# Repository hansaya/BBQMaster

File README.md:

# BBQMaster
8 channel temperature monitor for barbecuing.

# Features
* 4 NTC thermistor channels.
* 4 K-type thermocouple channels.
* Web interface to monitor the temperatures.
* MQTT support with hassio auto discovery.
* OTA updates.
* Web portal.

# Background
I got into smoking meat last few years and figured out maintaining the temperature is a big part of getting juicy results. Like everyone else, I do not have patience to stay right next to the smoker to monitor the temps. Specially if you have a cheaper lower-end smoker; monitoring the temperature is crucial. The usual solution is to buy a wireless temp monitor out of Amazon so if you find one that works for you, go for it. My solution here is expensive, close to 100$. I ended up creating this project because I broke two sub 50$ sensors and a upgrade will cost around 100$. Hence I decided to make one knowing I can create one less than 100$ plus I had fun creating it.

I had few requirements.
1) Monitor temperature over a web interface or a app.
2) Wireless.
3) Enough probes to monitor every corner of a brisket.
4) Be able to monitor the inside of the smoker and maybe the fire box.

Knowing the requirements, I decided to go with
1) 4 NTC probe inputs since its easy to find commercial probes online.
2) 4 thermocouple inputs for higher temperature monitoring. Why? NTC probes cannot handle high heat. They will degrade really fast when you put them over 300F.
3) Use esp32 as the brain because its cheap and easy to program.

# How to order and build the board
Board files are in "boards/" folder. Design in Eagle and you can just drop the zip file located in baord/bbqsensor/cam/ into jlcpcb.com to get them made.

Board design:
* 100mmx54mm 2-layer board.
* Jelly bean parts are 603 or above.
* Uses CP2104 as the USB interface.
* Buck coveter based on TPS54331DR. This will allow 9v-24v input.
* Lipo charging based on MCP73831.
* 3v3 Regulator based on AP2112.
* Thermocouple input handled by OneWire MAX3185.
* NTC thermistors are monitored by ADS1115 ADC for better accuracy.
* ESP32 as the brain.
* Terminal block connectors for easy connections.

For the bom, look at the schematic.

DISCLAIMER:
I'm a amature designer. I would recommend going over the schematic before ordering.

## Probes

### NTC
Most common replacement bbq probes will work. I bought https://www.ebay.com/itm/Chugod-Grilling-BBQ-Meat-Thermometer-Probe-Replacement-Temperature-Probes-4-Pa/402310429902?hash=item5dab91fcce:g:aDoAAOSwulde-Xr3

### K-type
You can buy any shape or size you want. However it is very hard to find probes designed for food. I would recommend use the thermocouple probes just to measure the inside temperature or firebox temperature.

# How to compile.
1) Download and install vscode with platformio. https://platformio.org/
2) Modify the platformio.ini file to either use serial port or use over the air updates.
3) If you are using Windows to compile, you might run into an compiler error because of Timelib. There are two headers named time.h in esp32 core and Time.h in Arduino timelib. These two looks the same to the compiler in windows because windows file names are case insensitive. Solution is to delete .pio/libdeps/myenv/Time/Time.h. More info https://github.com/esp8266/Arduino/issues/2341
4) Press upload.
5) Upload SPIFF image by running the vscode task "Upload File System Image". You can get to the task list from the left platformio panel or by typing "CTRL+SHIFT+P->Run task->platformio->Upload file system image".

# How to configure.
Firmware needs to know the MQTT server configuration. This can be done using WIFI manager portal. 
When you upload the code, if there is no previous credentials saved in the memory, WIFI AP will starts to broadcast using the name BBQ_Master. Connect to it and use the web portal to enter in the WIFI info as well as MQTT server address and the port. This creates a file in SPIFF called config.json. If you failed to enter the correct information or wants to modify the configuration later, create a file name config.json with data/ folder then use the "Upload file system Image" task to push the new file out.
config.json should looks like:
``
{"mqtt_server":"example.com", "mqtt_port":"1883"}
``

## Home Assistant
Turn on MQTT auto discovery https://www.home-assistant.io/docs/mqtt/discovery/. If esp32 connected to the MQTT server then hassio will automatically discover the device. If you are using non default discovery_prefix within hassio then change MQTT_HOME_ASSISTANT_DISCOVERY_PREFIX within the code reflect it.

# Known issues
* Forgot to add a LED indicator to the board.
* There is no way to turn off. As a workaround I attached a switch in series with the battery.
* Pubsub library only let you add a one "will" message. Because of this hassio sometimes fails to put all temperature sensor into unavailable state when disconnecting power from the device.
* Web interface theme functionality is broken.

# Todo
* Clean up the web interface.
* Add the ability to configure the temperature probe names through the web interface.
* Ability to calibrate the temperature probes using the web interface.
* Add a proper gauge to the battery indicator in the web interface.

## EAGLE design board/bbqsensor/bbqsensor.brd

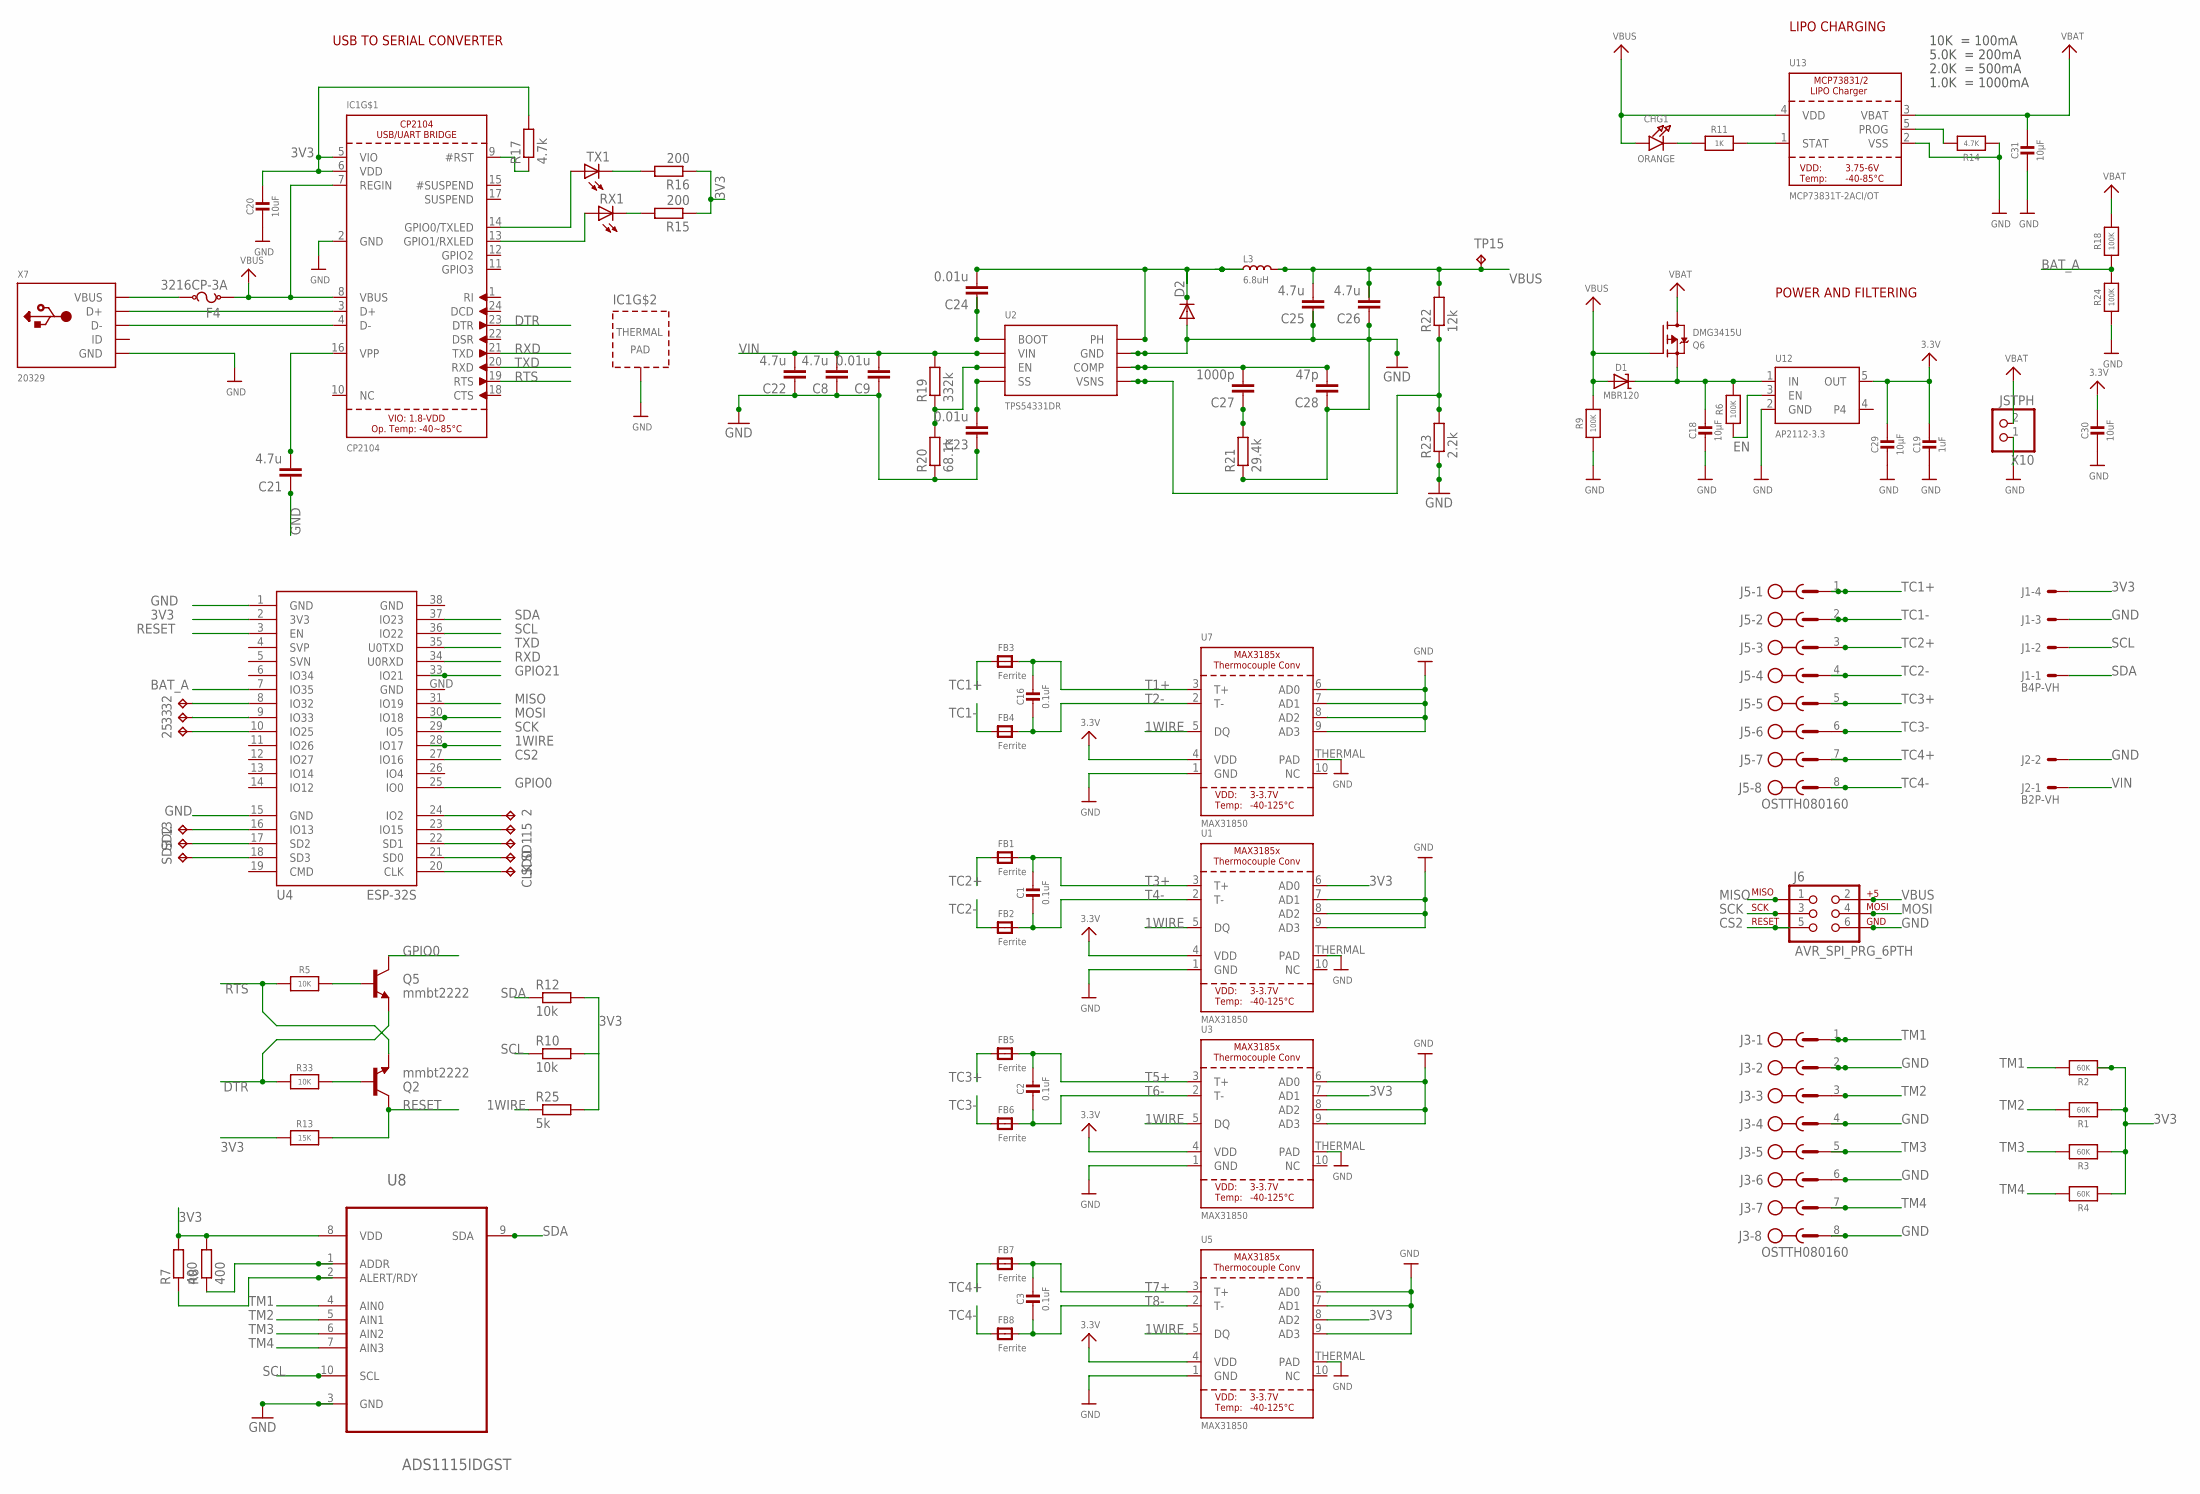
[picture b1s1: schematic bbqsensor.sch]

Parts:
2, 13, 15, 25, 32, 33: TPB1,27; B1,27
C1, C2, C3, C16: 0.1uF; 0805-NO
C8, C22, C25, C26: 4.7u; C1206
C9, C23, C24: 0.01u; C1206
C18, C29, C31: 10µF; 0805-NO
C19: 1uF; 0603-NO
C20, C30: 10uF; 0805-NO
C21: 4.7u; C1005
C27: 1000p; C1206
C28: 47p; C1206
CHG1: ORANGE; CHIPLED_0805_NOOUTLINE
CLK: TPB1,27; B1,27
D1: MBR120; SOD-123
D2: DIODE-DO214AA; DO214AA
F4: 3216CP-3A
FB1, FB2, FB3, FB4, FB5, FB6, FB7, FB8: Ferrite; 0805
IC1: CP2104; QFN24_4MM_SMSC
J1: B4P-VH; B4P
J2: B2P-VH; B2P
J3, J5: OSTTH080160; EDSTL130-08
J6: AVR_SPI_PRG_6PTH; 2X3
L3: 6.8uH; L1813
Q2, Q5: mmbt2222; SOT23-3
Q6: DMG3415U; SOT23-R
R1, R2, R3, R4: 60K; 0603-NO
R5, R33: 10K; 0603-NO
R6, R9, R18, R24: 100K; 0603-NO
R7, R8: 400; R0603
R10, R12: 10k; R0603
R11: 1K; 0603-NO
R13: 15K; 0603-NO
R14: 4.7K; 0603-NO
R15, R16: 200; R0603
R17: 4.7k; R0603
R19: 332k; R0603
R20: 68.1k; R0603
R21: 29.4k; R0603
R22: 12k; R0603
R23: 2.2k; R0603
R25: 5k; R0603
RX1: LEDSML0805; SML0805
SD0, SD1, SD2, SD3: TPB1,27; B1,27
TP15: TPB1,27; B1,27
TX1: LEDSML0805; SML0805
U1, U3, U5, U7: MAX31850; TDFN10_3X4MM
U2: TPS54331DR; SOIC-8
U4: ESP-32S
U8: ADS1115IDGST; SOP50P490X110-10N
U12: AP2112-3.3; SOT23-5
U13: MCP73831T-2ACI/OT; SOT23-5
X7: 20329; 4UCONN_20329_V2
X10: JSTPH; JSTPH2

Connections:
1WIRE: R25.1, U1.5 (DQ), U3.5 (DQ), U4.28 (IO17), U5.5 (DQ), U7.5 (DQ)
3V3: C19.1, C20.1, C29.1, C30.1, IC1.5 (VIO), IC1.6 (VDD), J1.4, R1.1, R2.1, R3.1, R4.1, R7.2, R8.2, R10.2, R12.2, R13.1, R15.1, R16.1, R17.2, R25.2, U1.4 (VDD), U1.6 (AD0), U3.4 (VDD), U3.7 (AD1), U4.2 (3V3), U5.4 (VDD), U5.8 (AD2), U7.4 (VDD), U8.8 (VDD), U12.5 (OUT)
BAT_A: R18.1, R24.2, U4.7 (IO35)
CS2: J6.5, U4.27 (IO16)
DTR: IC1.23 (DTR), Q5.2 (E), R33.1
EN: R6.1, U12.3 (EN)
GND: C8.1, C9.1, C18.2, C19.2, C20.2, C21.1, C22.1, C23.1, C25.1, C26.1, C28.1, C29.2, C30.2, C31.2, D2.A, IC1.2 (GND), IC1.THERM (TP), J1.3, J2.2, J3.2, J3.4, J3.6, J3.8, J6.6, R9.1, R14.1, R20.1, R21.1, R23.1, R24.1, U1.1 (GND), U1.7 (AD1), U1.8 (AD2), U1.9 (AD3), U1.THERMAL (PAD), U2.7 (GND), U3.1 (GND), U3.6 (AD0), U3.8 (AD2), U3.9 (AD3), U3.THERMAL (PAD), U4.1 (GND), U4.15 (GND), U4.38 (GND), U4.GND, U5.1 (GND), U5.6 (AD0), U5.7 (AD1), U5.9 (AD3), U5.THERMAL (PAD), U7.1 (GND), U7.6 (AD0), U7.7 (AD1), U7.8 (AD2), U7.9 (AD3), U7.THERMAL (PAD), U8.3 (GND), U12.2 (GND), U13.2 (VSS), X7.BASE@1 (GND), X7.BASE@2 (GND), X7.GND, X7.SPRT@1 (GND), X7.SPRT@2 (GND), X7.SPRT@3 (GND), X7.SPRT@4 (GND), X10.1
GPIO0: Q5.3 (C), U4.25 (IO0)
GPIO21: U4.33 (IO21)
MISO: J6.1, U4.31 (IO19)
MOSI: J6.4, U4.30 (IO18)
unnamed: 32.TP, U4.8 (IO32)
unnamed: 33.TP, U4.9 (IO33)
unnamed: 25.TP, U4.10 (IO25)
unnamed: 2.TP, U4.24 (IO2)
unnamed: 15.TP, U4.23 (IO15)
unnamed: 13.TP, U4.16 (IO13)
unnamed: SD1.TP, U4.22 (SD1)
unnamed: SD0.TP, U4.21 (SD0)
unnamed: CLK.TP, U4.20 (CLK)
unnamed: SD3.TP, U4.18 (SD3)
unnamed: SD2.TP, U4.17 (SD2)
unnamed: R7.1, U8.2 (ALERT/RDY)
unnamed: R8.1, U8.1 (ADDR)
unnamed: IC1.3 (D+), X7.D+
unnamed: IC1.4 (D-), X7.D-
unnamed: IC1.13 (GPIO1/RXLED), RX1.A
unnamed: R15.2, RX1.C
unnamed: R16.2, TX1.C
unnamed: IC1.14 (GPIO0/TXLED), TX1.A
unnamed: C18.1, D1.C, Q6.2 (S), R6.2, U12.1 (IN)
unnamed: CHG1.C, R11.1
unnamed: R11.2, U13.1 (STAT)
unnamed: R14.2, U13.5 (PROG)
unnamed: C21.2, IC1.16 (VPP)
unnamed: IC1.9 (#RST), R17.1
unnamed: F4.2, X7.VBUS
unnamed: Q2.1 (B), R33.2
unnamed: Q5.1 (B), R5.2
unnamed: C23.2, U2.4 (SS)
unnamed: R19.1, R20.2, U2.3 (EN)
unnamed: C24.1, U2.1 (BOOT)
unnamed: C24.2, D2.C, L3.1, U2.8 (PH)
unnamed: C27.2, C28.2, U2.6 (COMP)
unnamed: C27.1, R21.2
unnamed: R22.1, R23.2, U2.5 (VSNS)
RESET: Q2.3 (C), R13.2, U4.3 (EN)
RTS: IC1.19 (RTS), Q2.2 (E), R5.1
RXD: IC1.21 (TXD), U4.34 (U0RXD)
SCK: J6.3, U4.29 (IO5)
SCL: J1.2, R10.1, U4.36 (IO22), U8.10 (SCL)
SDA: J1.1, R12.1, U4.37 (IO23), U8.9 (SDA)
T1+: C16.1, FB3.2, U7.3 (T+)
T2-: C16.2, FB4.2, U7.2 (T-)
T3+: C1.1, FB1.2, U1.3 (T+)
T4-: C1.2, FB2.2, U1.2 (T-)
T5+: C2.1, FB5.2, U3.3 (T+)
T6-: C2.2, FB6.2, U3.2 (T-)
T7+: C3.1, FB7.2, U5.3 (T+)
T8-: C3.2, FB8.2, U5.2 (T-)
TC1+: FB3.1, J5.1
TC1-: FB4.1, J5.2
TC2+: FB1.1, J5.3
TC2-: FB2.1, J5.4
TC3+: FB5.1, J5.5
TC3-: FB6.1, J5.6
TC4+: FB7.1, J5.7
TC4-: FB8.1, J5.8
TM1: J3.1, R2.2, U8.4 (AIN0)
TM2: J3.3, R1.2, U8.5 (AIN1)
TM3: J3.5, R3.2, U8.6 (AIN2)
TM4: J3.7, R4.2, U8.7 (AIN3)
TXD: IC1.20 (RXD), U4.35 (U0TXD)
VBAT: C31.1, Q6.3 (D), R18.2, U13.3 (VBAT), X10.2
VBUS: C25.2, C26.2, CHG1.A, D1.A, F4.1, IC1.7 (REGIN), IC1.8 (VBUS), J6.2, L3.2, Q6.1 (G), R9.2, R22.2, TP15.TP, U13.4 (VDD)
VIN: C8.2, C9.2, C22.2, J2.1, R19.2, U2.2 (VIN)

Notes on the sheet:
USB TO SERIAL CONVERTER
POWER AND FILTERING
10K = 100mA
5.0K = 200mA
2.0K = 500mA
1.0K = 1000mA
LIPO CHARGING

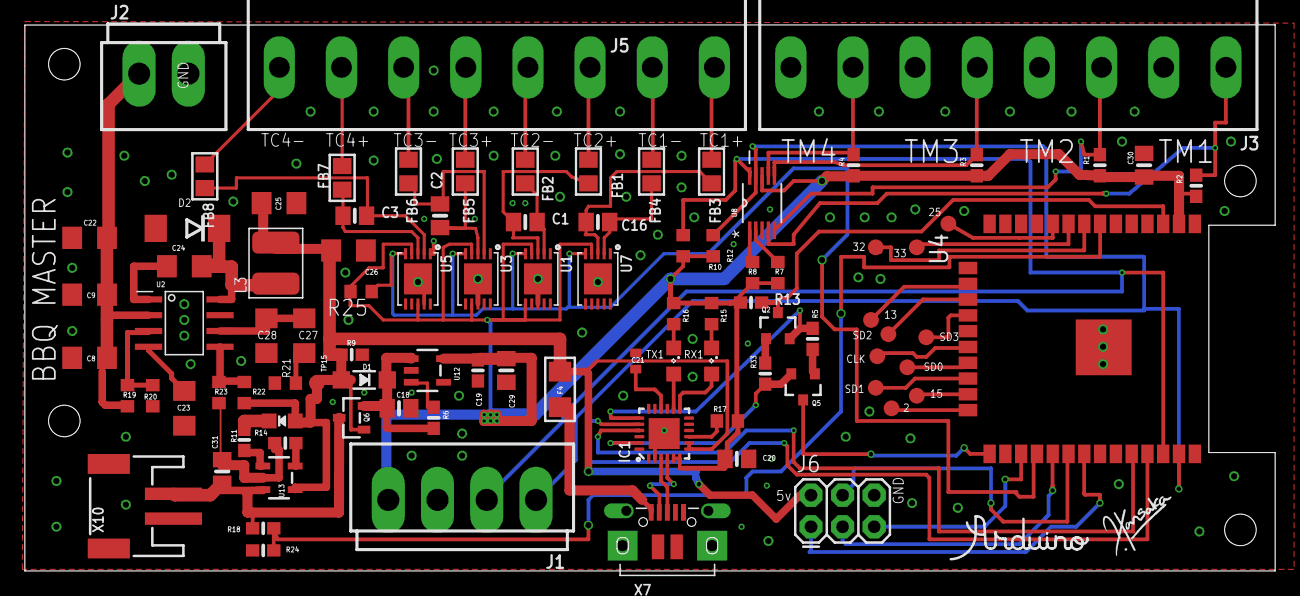
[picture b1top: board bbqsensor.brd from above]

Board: 2 copper layers, 100.6 x 43.9 mm, 95 parts (0 on the bottom side), 75 nets.

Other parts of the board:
U$5: SIGNATURE
U$6: LOGO-A

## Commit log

2020-07-04 init commit
2020-07-04 board files
2020-07-06 MQTT integration
2020-07-06 Clean up
2020-07-06 ignore vscode files
2020-07-06 Starting the doc
2020-07-07 More documentation
2020-07-07 Grammer!
2020-07-07 Create LICENSE

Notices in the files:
parts and their libraries:
microbuilder: This work is placed in the public domain, and may be freely used for commercial and non-commercial work with the following conditions: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
con-ost: Copyright (C) 2008, Bob Starr
SparkFun: Licensing: CC v3.0 Share-Alike You are welcome to use this library for commercial purposes.
